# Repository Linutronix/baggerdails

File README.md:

<!-- SPDX-FileCopyrightText: 2023 Linutronix GmbH <info@linutronix.de> -->
<!-- SPDX-License-Identifier: CERN-OHL-S-2.0 -->

# baggerdails - A RPi HAT for a trade fair demo

The baggerdails RPi HAT is a small PCB containing 14 LEDs, a 256k serial
EEPROM, an ATECC608 Security Verification / Encryption IC, two SPI display
connectors and last but not least an USB serial converter attached to a
full-size 40W GPIO connector as described in the
[ADD-ON BOARDS AND HATs specification](https://github.com/raspberrypi/hats).

## License rules

baggerdails is provided under the terms of the CERN-OHL-S license version 2
as provided in the LICENSES/CERN-OHL-S-2.0 file.

Instead of adding license boilerplates to the individual files, baggerdails
uses SPDX license identifiers, which are machine parseable and considered
legaly equivalent.

The SPDX license identifier in baggerdails shall be added at the first possible
line in a file which can contain a comment. This is normally the first line
except for scripts. Scripts require the #!PATH_TO_INTERPRETER tag in the
first line; place the SPDX identifier into the second line.

The SPDX license identifier is added in form of a comment.

## Copyright and License

Copyright Linutronix GmbH 2023.

This source describes Open Hardware and is licensed under the CERN-OHL-S v2.
You may redistribute and modify this source and make products using it
under the terms of the CERN-OHL-S v2 (https://ohwr.org/cern_ohl_s_v2.txt).

This source is distributed WITHOUT ANY EXPRESS OR IMPLIED WARRANTY,
INCLUDING OF MERCHANTABILITY, SATISFACTORY QUALITY AND FITNESS FOR A
PARTICULAR PURPOSE.

Please see the CERN-OHL-S v2 for applicable conditions.

Source location: https://github.com/linutronix/baggerdails

As per CERN-OHL-S v2 section 4, should You produce hardware based
on this source, You must where practicable maintain the Source Location
visible on the external case of the baggerdails or other products you make
using this source.

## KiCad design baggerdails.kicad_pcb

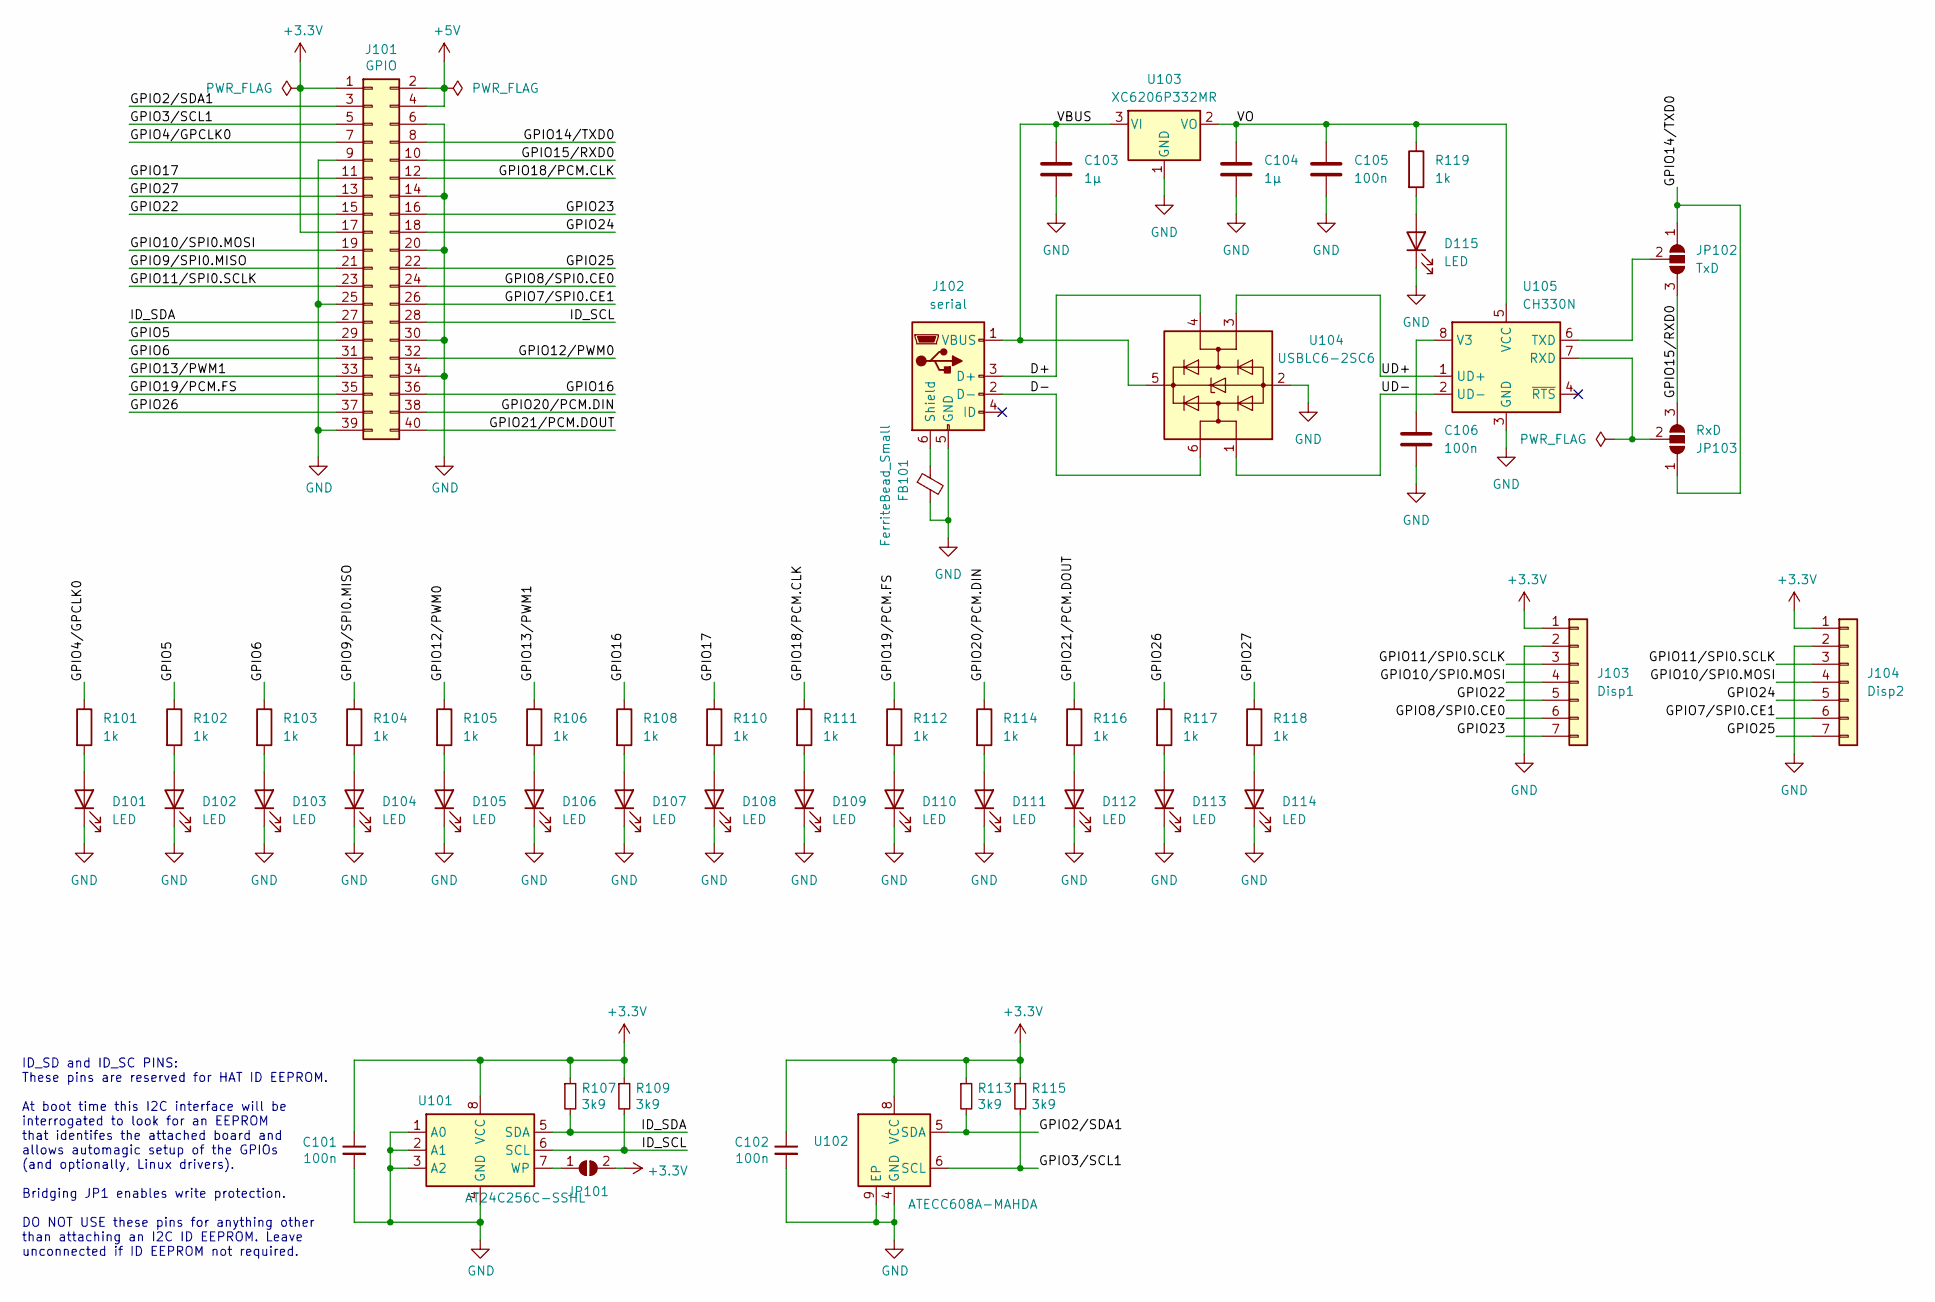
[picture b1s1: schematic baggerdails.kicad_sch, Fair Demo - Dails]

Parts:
C101, C102, C105, C106: 100n; C_0402_1005Metric; mpn GRM155R71H104KE14D; lcsc# C77020
C103, C104: 1µ; C_0805_2012Metric; mpn GRT21BR71H105KE01L; lcsc# C701194
D101, D102, D103, D104, D105, D106, D107, D108, D109, D110, D111, D112, D113, D114, D115: LED; LED_0603_1608Metric; mpn 19-217/BHC-ZL1M2RY/3T; lcsc# C72041
FB101: FerriteBead_Small; L_0402_1005Metric; mpn BLM15AG121SN1D; lcsc# C85812
J101: GPIO; PinSocket_2x20_P2.54mm_Vertical; mpn DS1023-2*20S21
J102: serial; USB_Micro-B_Molex-105017-0001; mpn 1050171001; digikey# WM11262CT-ND
J103: Disp1; PinSocket_1x07_P2.54mm_Vertical; mpn DS1023-1*7S21
J104: Disp2; PinSocket_1x07_P2.54mm_Vertical; mpn DS1023-1*7S21
JP101: ID_WP; SolderJumper-2_P1.3mm_Open_Pad1.0x1.5mm; mpn DNP
JP102: TxD; SolderJumper-3_P1.3mm_Open_Pad1.0x1.5mm_NumberLabels; mpn DNP
JP103: RxD; SolderJumper-3_P1.3mm_Open_Pad1.0x1.5mm_NumberLabels; mpn DNP
R101, R102, R103, R104, R105, R106, R108, R110, R111, R112, R114, R116, R117, R118, R119: 1k; R_0402_1005Metric; mpn RC0402JR-071KL; digikey# 311-1.0KJRCT-ND
R107, R109, R113, R115: 3k9; R_0402_1005Metric; mpn AF0402FR-073K9L; lcsc# C144037
U101: AT24C256C-SSHL; SOIC-8_3.9x4.9mm_P1.27mm; mpn AT24C256C-SSHL-T; lcsc# C6482
U102: ATECC608A-MAHDA; DFN-8-1EP_3x2mm_P0.5mm_EP1.3x1.5mm; mpn ATECC608A-MAHDA-T; lcsc# C616909
U103: XC6206P332MR; SOT-23-3; mpn XC6206P332MR; lcsc# C2897477
U104: USBLC6-2SC6; SOT-23-6; mpn USBLC6-2SC6; lcsc# C7519
U105: CH330N; SOIC-8_3.9x4.9mm_P1.27mm; mpn CH330N; lcsc# C108996

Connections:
+3.3V: C101.1, C102.1, J101.1, J101.17, J103.1, J104.1, JP101.2 (B), R107.1, R109.1, R113.1, R115.1, U101.8 (VCC), U102.8 (VCC)
+5V: J101.2, J101.4
/D+: J102.3 (D+), U104.4 (I/O2)
/D-: J102.2 (D-), U104.6 (I/O1)
/GPIO2/SDA1: J101.3, R113.2, U102.5 (SDA)
/GPIO3/SCL1: J101.5, R115.2, U102.6 (SCL)
/GPIO4/GPCLK0: J101.7, R101.1
/GPIO5: J101.29, R102.1
/GPIO6: J101.31, R103.1
/GPIO7/SPI0.CE1: J101.26, J104.6
/GPIO8/SPI0.CE0: J101.24, J103.6
/GPIO9/SPI0.MISO: J101.21, R104.1
/GPIO10/SPI0.MOSI: J101.19, J103.4, J104.4
/GPIO11/SPI0.SCLK: J101.23, J103.3, J104.3
/GPIO12/PWM0: J101.32, R105.1
/GPIO13/PWM1: J101.33, R106.1
/GPIO14/TXD0: J101.8, JP102.1 (A), JP103.1 (A)
/GPIO15/RXD0: J101.10, JP102.3 (B), JP103.3 (B)
/GPIO16: J101.36, R108.1
/GPIO17: J101.11, R110.1
/GPIO18/PCM.CLK: J101.12, R111.1
/GPIO19/PCM.FS: J101.35, R112.1
/GPIO20/PCM.DIN: J101.38, R114.1
/GPIO21/PCM.DOUT: J101.40, R116.1
/GPIO22: J101.15, J103.5
/GPIO23: J101.16, J103.7
/GPIO24: J101.18, J104.5
/GPIO25: J101.22, J104.7
/GPIO26: J101.37, R117.1
/GPIO27: J101.13, R118.1
/ID_SCL: J101.28, R109.2, U101.6 (SCL)
/ID_SDA: J101.27, R107.2, U101.5 (SDA)
/UD+: U104.3 (I/O2), U105.1 (UD+)
/UD-: U104.1 (I/O1), U105.2 (UD-)
/VBUS: C103.1, J102.1 (VBUS), U103.3 (VI), U104.5 (VBUS)
/VO: C104.1, C105.1, R119.1, U103.2 (VO), U105.5 (VCC)
GND: C101.2, C102.2, C103.2, C104.2, C105.2, C106.2, D101.1 (K), D102.1 (K), D103.1 (K), D104.1 (K), D105.1 (K), D106.1 (K), D107.1 (K), D108.1 (K), D109.1 (K), D110.1 (K), D111.1 (K), D112.1 (K), D113.1 (K), D114.1 (K), D115.1 (K), FB101.2, J101.6, J101.9, J101.14, J101.20, J101.25, J101.30, J101.34, J101.39, J102.5 (GND), J103.2, J104.2, U101.1 (A0), U101.2 (A1), U101.3 (A2), U101.4 (GND), U102.4 (GND), U102.9 (EP), U103.1 (GND), U104.2 (GND), U105.3 (GND)
unnamed: D101.2 (A), R101.2
unnamed: D102.2 (A), R102.2
unnamed: D103.2 (A), R103.2
unnamed: D104.2 (A), R104.2
unnamed: D105.2 (A), R105.2
unnamed: D106.2 (A), R106.2
unnamed: D107.2 (A), R108.2
unnamed: D108.2 (A), R110.2
unnamed: D109.2 (A), R111.2
unnamed: D110.2 (A), R112.2
unnamed: D111.2 (A), R114.2
unnamed: D112.2 (A), R116.2
unnamed: D113.2 (A), R117.2
unnamed: D114.2 (A), R118.2
unnamed: D115.2 (A), R119.2
unnamed: FB101.1, J102.6 (Shield)
unnamed: JP101.1 (A), U101.7 (WP)
unnamed: JP102.2 (C), U105.6 (TXD)
unnamed: JP103.2 (C), U105.7 (RXD)
unnamed: C106.1, U105.8 (V3)

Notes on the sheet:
ID_SD and ID_SC PINS: These pins are reserved for HAT ID EEPROM. At boot time this I2C interface will be interrogated to look for an EEPROM that identifes the attached board and allows automagic setup of the GPIOs (and optionally, Linux drivers). Bridging JP1 enables write protection. DO NOT USE th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

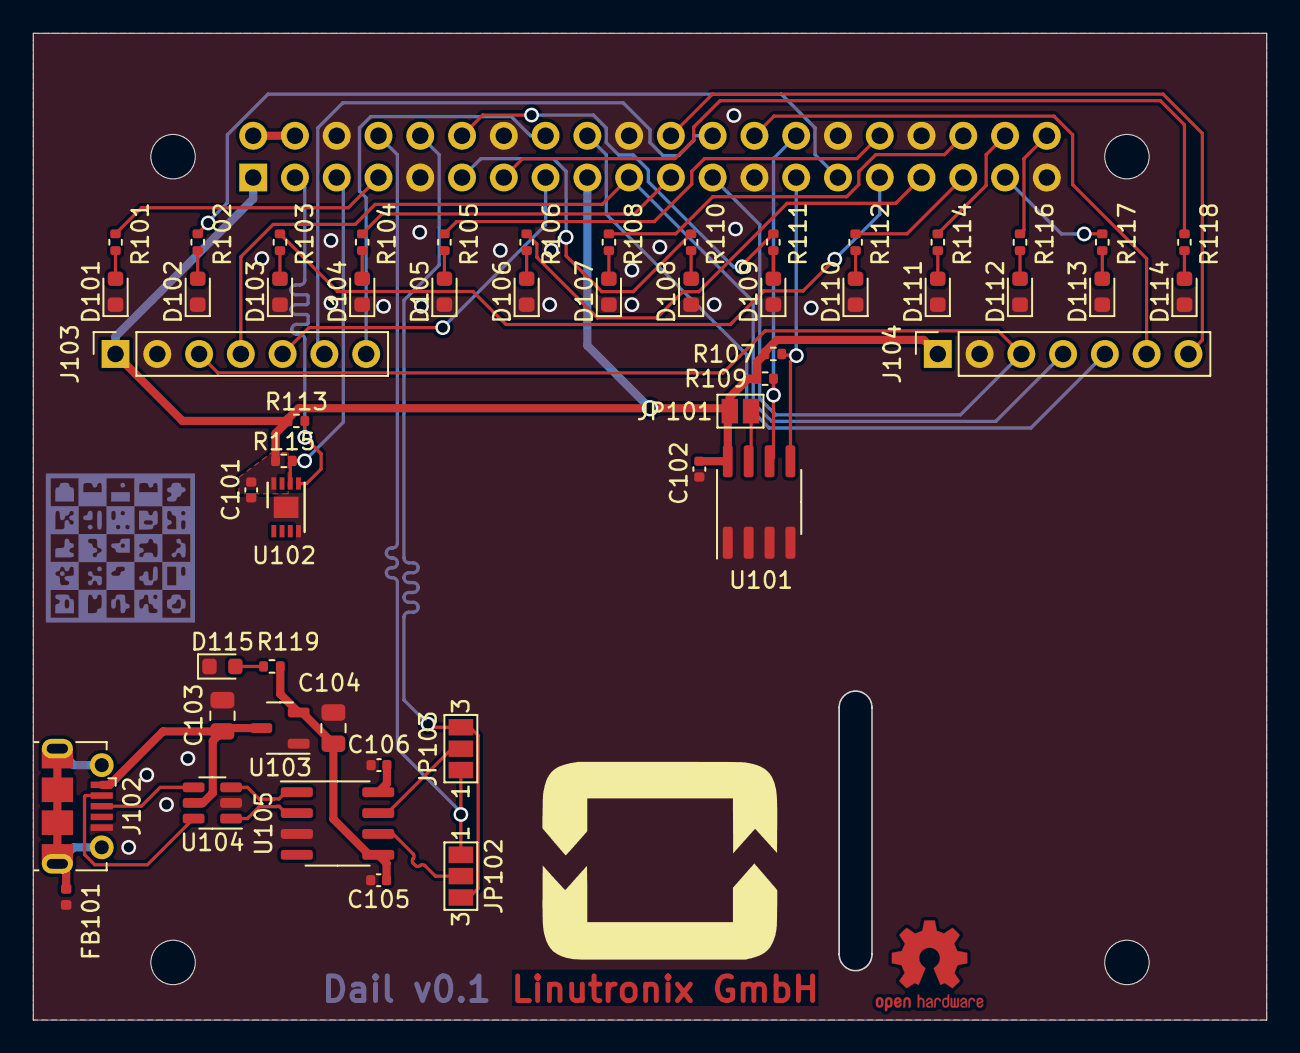
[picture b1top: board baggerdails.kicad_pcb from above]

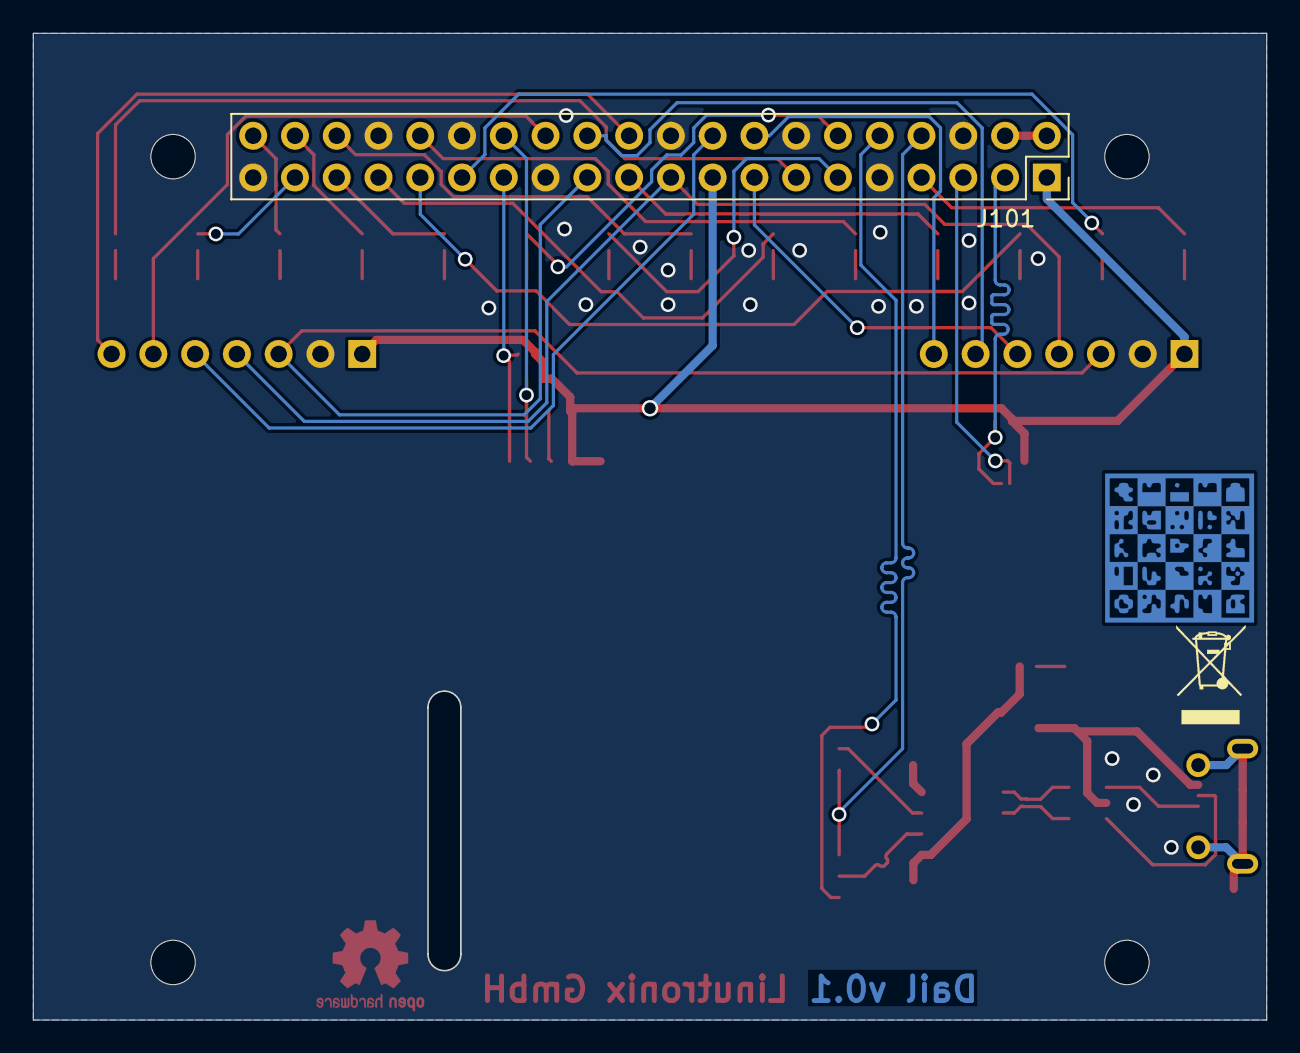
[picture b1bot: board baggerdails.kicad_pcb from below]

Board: 2 copper layers, 75.0 x 60.0 mm, 61 parts (3 on the bottom side), 57 nets.

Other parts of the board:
Eurovibes: LOGO
Linutronix: LOGO; linutronix
MH1, MH2, MH3, MH4: MountingHole_2.7mm_M2.5
OSHW: OSHW-Logo2_7.3x6mm_Copper
WEEE: WEEE-Logo_4.2x6mm_SilkScreen

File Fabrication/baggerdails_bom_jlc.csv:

"Comment","Designator","Footprint","LCSC Part #"
"100n","C101,C102,C105,C106","C_0402_1005Metric","C77020"
"1µ","C103,C104","C_0805_2012Metric","C701194"
"LED","D101,D102,D103,D104,D105,D106,D107,D108,D109,D110,D111,D112,D113,D114,D115","LED_0603_1608Metric","C72041"
"FerriteBead_Small","FB101","L_0402_1005Metric","C85812"
"serial","J102","USB_Micro-B_Molex-105017-0001","C505111"
"1k","R101,R102,R103,R104,R105,R106,R108,R110,R111,R112,R114,R116,R117,R118,R119","R_0402_1005Metric","C114759"
"3k9","R107,R109,R113,R115","R_0402_1005Metric","C144037"
"AT24C256C-SSHL","U101","SOIC-8_3.9x4.9mm_P1.27mm","C6482"
"ATECC608A-MAHDA","U102","DFN-8-1EP_3x2mm_P0.5mm_EP1.3x1.5mm","C616909"
"CH330N","U105","SOIC-8_3.9x4.9mm_P1.27mm","C108996"
"USBLC6-2SC6","U104","SOT-23-6","C7519"
"XC6206P332MR","U103","SOT-23-3","C2897477"

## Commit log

2023-08-29 Initial
2023-08-30 Add Logo
2023-08-30 Add github actions
2023-11-14 Add license CERN-OHL-S-2.0 file
2023-11-14 Add README
2023-11-14 Initial gh pages
    Add gh pages for project documentation.
2023-11-14 Deploying to gh-pages from @ linutronix/baggerdails@bca094cd72c64d8c07704386ab8038f725105cda 🚀
2023-11-21 Deploying to gh-pages from @ Linutronix/baggerdails@7c4841d706310cc8ecd59bd94692b14250e6274f 🚀

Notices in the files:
baggerdails.kicad_sch:
This work is licensed under the CERN-OHL-S v2
